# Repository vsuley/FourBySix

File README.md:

# The Ganesha Keyboard

The Ganesha is a keyboard inspired by and forked from the amazing Corne keyboard. After having built a number
of Corne KBs, I need something that has the number row. There are other forks like Lily58 (and further still, like
Sofle, Orbit etc) but they have certain features that I have a strong preference to remove (mirrored PCB, unutilized
component designations, dependence on Pro Micro etc).

## Major Design Goals
### User's POV
1. Split ortho-linear layout.
2. Have a dedicated numbers row.
3. No bigger than a standard print of Moby Dick when packed.
4. Enable USB-C without the added cost of an Elite-C board.
5. Per Key and ambient LEDs.

### Builder's POV
1. Enable factory assembly as much as possible (jlcpcb.com in my case)
2. Clean, self documenting PCB layout.
3. Compatible with low-profile switches and keycaps
4. Directly embedded atmega32u4
5. 4 layer PCB

## Dependencies
### KiCad libraries
You should clone https://github.com/foostan/kbd to get the symbol and footprint libraries used in these kicad projects.
1. Clone this repo and foostan/kbd
1. Install kicad.
1. Open ganesha.pro in Kicad.
1. Preferences > Manage Symbol Libraries
    1.  Hover over the folder looking icon below the table, it should say "Add existing table to library". 
    2.  Click that button.
    3.  Navigate to the symbol library located under kbd/kicad-symbols/
    4.  Add. 
1. Repeat the same process for footprint libraries.

## Starting Priorities
Calling out a few assumptions I will be starting with, but would like to expand when time permits.
1. Kailh Cherry MX hot swap sockets as switch anchors

## Why "Ganesha"?
Ganesha, in Hindu mythology, is the popular elephant headed deity whose images you may have seen. Aside from being the son 
of Lord Shiva, he is also the God of Wisdom and more pertinently, he is the scribe who penned down the great epic 
'Mahabharata' as sage Vyasa composed it.

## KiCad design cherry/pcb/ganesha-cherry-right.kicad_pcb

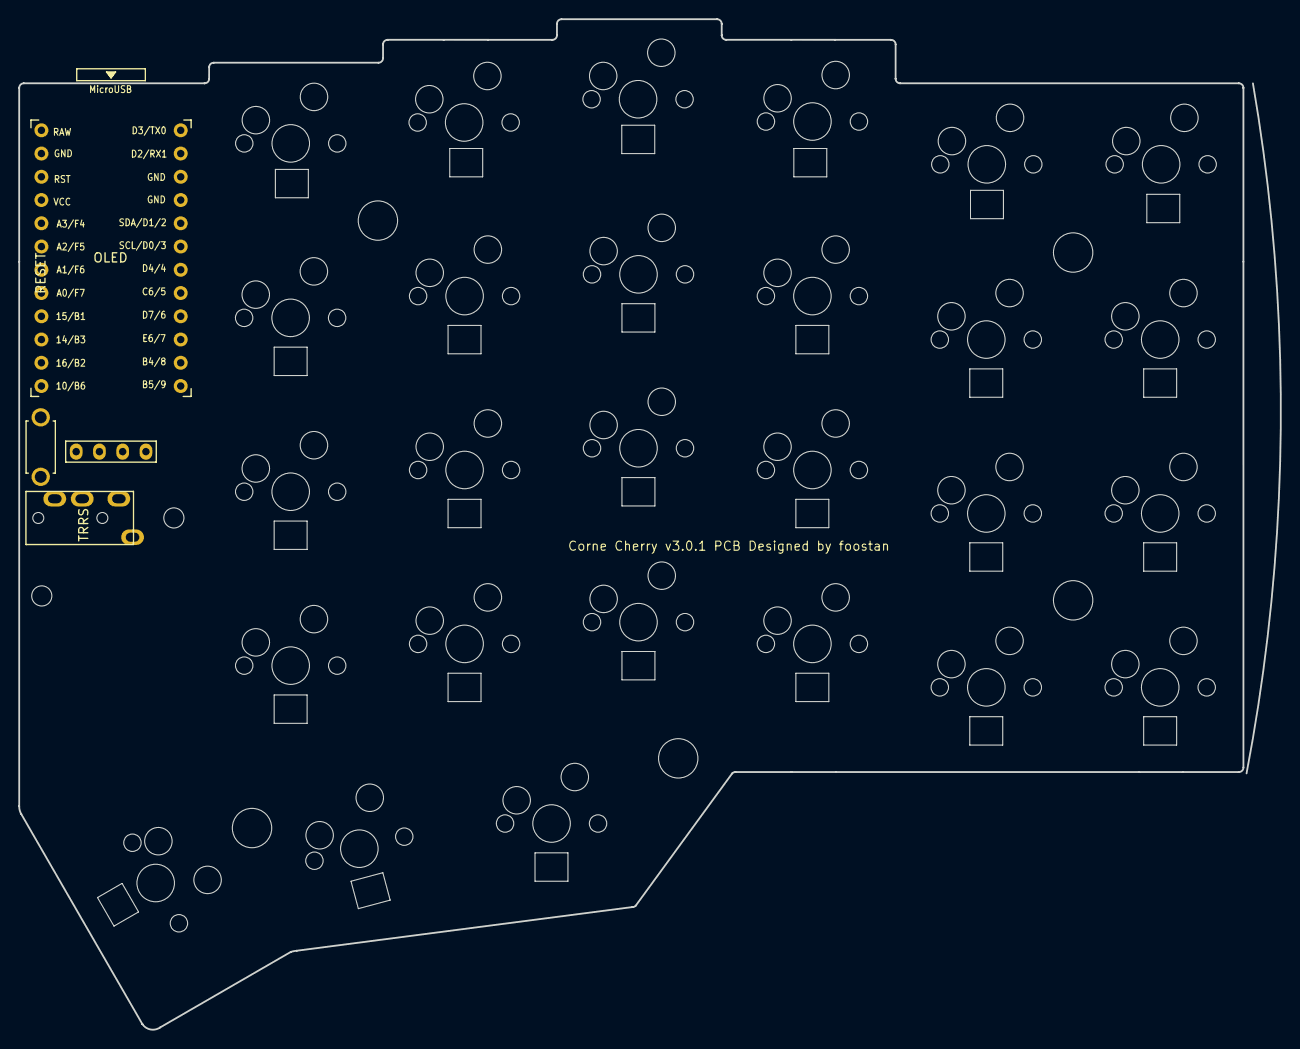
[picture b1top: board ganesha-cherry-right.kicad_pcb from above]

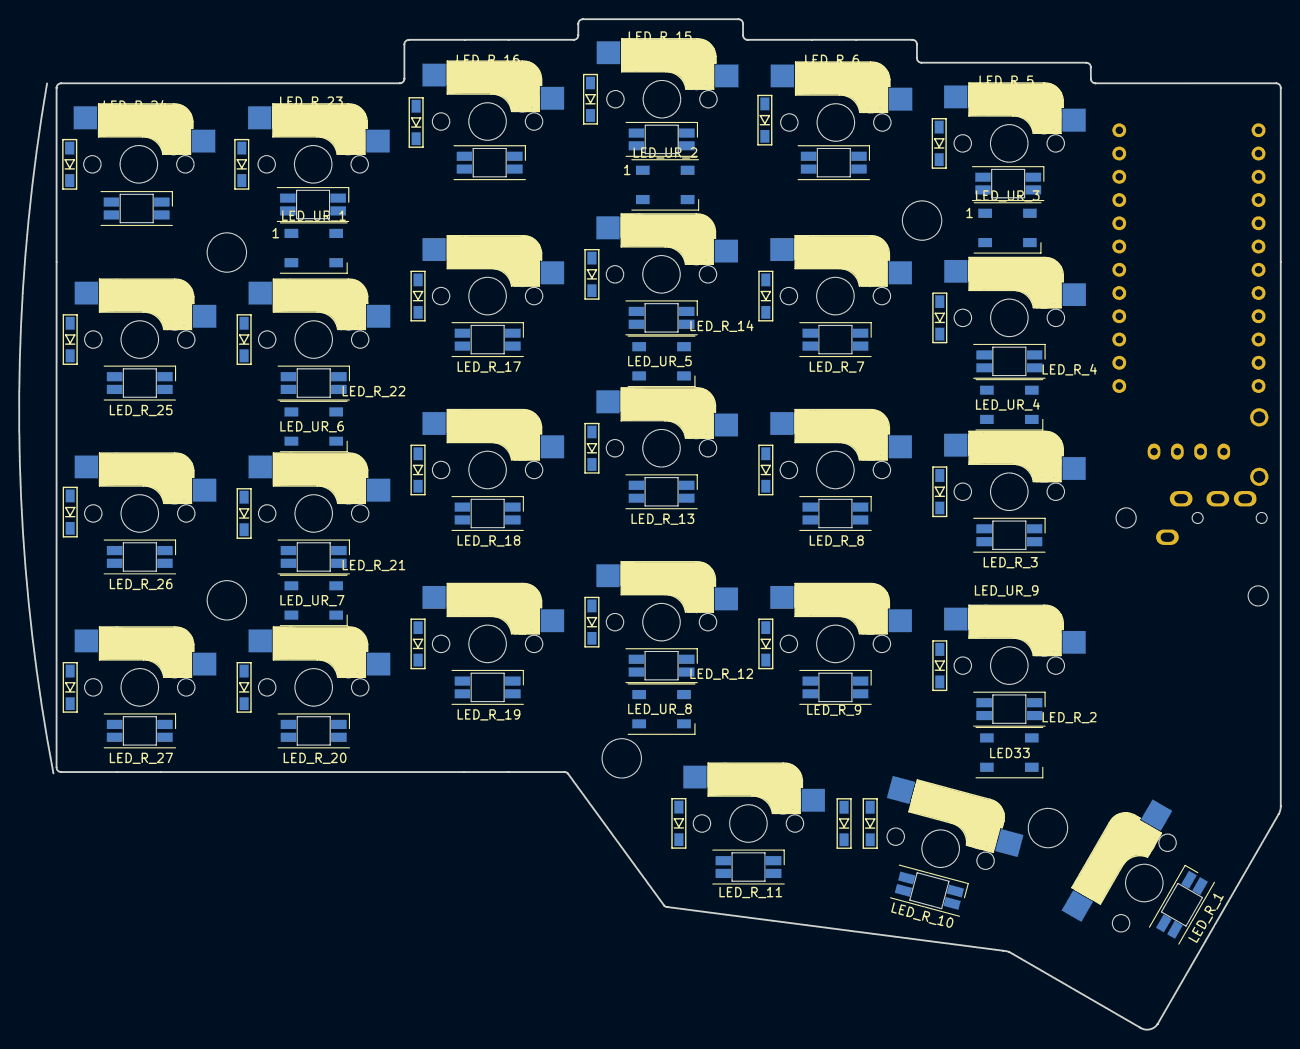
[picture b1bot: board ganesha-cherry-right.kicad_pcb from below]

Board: 2 copper layers, 137.8 x 110.4 mm, 101 parts (66 on the bottom side), 82 nets, no tracks yet.

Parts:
D_R1, D_R2, D_R3, D_R4, D_R5, D_R6, D_R7, D_R8, D_R9, D_R10, D_R11, D_R12, D_R13, D_R14, D_R15, D_R16, D_R17, D_R18, D_R19, D_R20, D_R21, D_R22, D_R23, D_R24, D_R25, D_R26, D_R27: D; D3_SMD_v2
J3: MJ-4PP-9; MJ-4PP-9_1side
J4: OLED; OLED_1side
LED_R_1, LED_R_2, LED_R_3, LED_R_4, LED_R_5, LED_R_6, LED_R_7, LED_R_8, LED_R_9, LED_R_10, LED_R_11, LED_R_12, LED_R_13, LED_R_14, LED_R_15, LED_R_16, LED_R_17, LED_R_18, LED_R_19, LED_R_20, LED_R_21, LED_R_22, LED_R_23, LED_R_24, LED_R_25, LED_R_26, LED_R_27: YS-SK6812MINI-E
LED_UR_1, LED_UR_2, LED_UR_3, LED_UR_4, LED_UR_5, LED_UR_6, LED_UR_7, LED_UR_8, LED_UR_9: WS2812B; LED_WS2812B_PLCC4_5.0x5.0mm_P3.2mm
RSW2: SW_PUSH; ResetSW_1side
Ref**: Val**; M2_HOLE_v2
Ref**#2, Ref**#3, Ref**#4, Ref**#5, Ref**#6, Ref**#7: Val**; M2_HOLE_v2
SW_R1, SW_R2, SW_R3, SW_R4, SW_R5, SW_R6, SW_R7, SW_R8, SW_R9, SW_R10, SW_R11, SW_R12, SW_R13, SW_R14, SW_R15, SW_R16, SW_R17, SW_R18, SW_R19, SW_R20, SW_R21, SW_R22, SW_R23, SW_R24, SW_R25, SW_R26: SW_PUSH; CherryMX_Hotswap
SW_R27: SW_PUSH; CherryMX_Hotswap_1.5u
U2: ProMicro; ProMicro_v3

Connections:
GND: LED_R_1.3, LED_R_2.3, LED_R_3.3, LED_R_4.3, LED_R_5.3, LED_R_6.3, LED_R_7.3, LED_R_8.3, LED_R_9.3, LED_R_10.3, LED_R_11.3, LED_R_12.3, LED_R_13.3, LED_R_14.3, LED_R_15.3, LED_R_16.3, LED_R_17.3, LED_R_18.3, LED_R_19.3, LED_R_20.3, LED_R_21.3, LED_R_22.3, LED_R_23.3, LED_R_24.3, LED_R_25.3, LED_R_26.3, LED_R_27.3, LED_UR_1.3, LED_UR_2.3, LED_UR_3.3, LED_UR_4.3, LED_UR_5.3, LED_UR_6.3, LED_UR_7.3, LED_UR_8.3, LED_UR_9.3
GNDA: J3.C, J4.4, RSW2.2, U2.3, U2.4, U2.23
LED_r: LED_UR_1.4, U2.1
unnamed: D_R1.2, SW_R1.2
unnamed: D_R2.2, SW_R2.2
unnamed: D_R3.2, SW_R3.2
unnamed: D_R4.2, SW_R4.2
unnamed: D_R5.2, SW_R5.2
unnamed: D_R6.2, SW_R6.2
unnamed: D_R7.2, SW_R7.2
unnamed: D_R8.2, SW_R8.2
unnamed: D_R9.2, SW_R9.2
unnamed: D_R10.2, SW_R10.2
unnamed: D_R11.2, SW_R11.2
unnamed: D_R12.2, SW_R12.2
unnamed: D_R13.2, SW_R13.2
unnamed: D_R14.2, SW_R14.2
unnamed: D_R15.2, SW_R15.2
unnamed: D_R16.2, SW_R16.2
unnamed: D_R17.2, SW_R17.2
unnamed: D_R18.2, SW_R18.2
unnamed: D_R19.2, SW_R19.2
unnamed: D_R20.2, SW_R20.2
unnamed: D_R21.2, SW_R21.2
unnamed: D_R22.2, SW_R22.2
unnamed: D_R23.2, SW_R23.2
unnamed: D_R24.2, SW_R24.2
unnamed: D_R25.2, SW_R25.2
unnamed: D_R26.2, SW_R26.2
unnamed: D_R27.2, SW_R27.2
unnamed: LED_R_1.2, LED_R_2.4
unnamed: LED_R_1.4, LED_UR_9.2
unnamed: LED_R_2.2, LED_R_3.4
unnamed: LED_R_3.2, LED_R_4.4
unnamed: LED_R_4.2, LED_R_5.4
unnamed: LED_R_5.2, LED_R_6.4
unnamed: LED_R_6.2, LED_R_7.4
unnamed: LED_R_7.2, LED_R_8.4
unnamed: LED_R_8.2, LED_R_9.4
unnamed: LED_R_10.2, LED_R_11.4
unnamed: LED_R_9.2, LED_R_10.4
unnamed: LED_R_11.2, LED_R_12.4
unnamed: LED_R_12.2, LED_R_13.4
unnamed: LED_R_13.2, LED_R_14.4
unnamed: LED_R_14.2, LED_R_15.4
unnamed: LED_R_15.2, LED_R_16.4
unnamed: LED_R_16.2, LED_R_17.4
unnamed: LED_R_17.2, LED_R_18.4
unnamed: LED_R_18.2, LED_R_19.4
unnamed: LED_R_19.2, LED_R_20.4
unnamed: LED_R_20.2, LED_R_21.4
unnamed: LED_R_21.2, LED_R_22.4
unnamed: LED_R_22.2, LED_R_23.4
unnamed: LED_R_23.2, LED_R_24.4
unnamed: LED_R_24.2, LED_R_25.4
unnamed: LED_R_25.2, LED_R_26.4
unnamed: LED_R_26.2, LED_R_27.4
unnamed: LED_UR_1.2, LED_UR_2.4
unnamed: LED_UR_2.2, LED_UR_3.4
unnamed: LED_UR_3.2, LED_UR_4.4
unnamed: LED_UR_4.2, LED_UR_5.4
unnamed: LED_UR_5.2, LED_UR_6.4
unnamed: LED_UR_6.2, LED_UR_7.4
unnamed: LED_UR_7.2, LED_UR_8.4
unnamed: LED_UR_8.2, LED_UR_9.4
SCL_r: J4.2, U2.6
SDA_r: J4.1, U2.5
VCC: LED_R_1.1, LED_R_2.1, LED_R_3.1, LED_R_4.1, LED_R_5.1, LED_R_6.1, LED_R_7.1, LED_R_8.1, LED_R_9.1, LED_R_10.1, LED_R_11.1, LED_R_12.1, LED_R_13.1, LED_R_14.1, LED_R_15.1, LED_R_16.1, LED_R_17.1, LED_R_18.1, LED_R_19.1, LED_R_20.1, LED_R_21.1, LED_R_22.1, LED_R_23.1, LED_R_24.1, LED_R_25.1, LED_R_26.1, LED_R_27.1, LED_UR_1.1, LED_UR_2.1, LED_UR_3.1, LED_UR_4.1, LED_UR_5.1, LED_UR_6.1, LED_UR_7.1, LED_UR_8.1, LED_UR_9.1
VDD: J3.D, J4.3, U2.21
col0_r: SW_R1.1, SW_R7.1, SW_R13.1, SW_R19.1, U2.20
col1_r: SW_R2.1, SW_R8.1, SW_R14.1, SW_R20.1, U2.19
col2_r: SW_R3.1, SW_R9.1, SW_R15.1, SW_R21.1, SW_R25.1, U2.18
col3_r: SW_R4.1, SW_R10.1, SW_R16.1, SW_R22.1, SW_R26.1, U2.17
col4_r: SW_R5.1, SW_R11.1, SW_R17.1, SW_R23.1, SW_R27.1, U2.16
col5_r: SW_R6.1, SW_R12.1, SW_R18.1, SW_R24.1, U2.15
data_r: J3.B, U2.2
reset_r: RSW2.1, U2.22
row0_r: D_R1.1, D_R2.1, D_R3.1, D_R4.1, D_R5.1, D_R6.1, U2.7
row1_r: D_R7.1, D_R8.1, D_R9.1, D_R10.1, D_R11.1, D_R12.1, U2.8
row2_r: D_R13.1, D_R14.1, D_R15.1, D_R16.1, D_R17.1, D_R18.1, U2.9
row3_r: D_R19.1, D_R20.1, D_R21.1, D_R22.1, D_R23.1, D_R24.1, U2.10
row4_r: D_R25.1, D_R26.1, D_R27.1, U2.11

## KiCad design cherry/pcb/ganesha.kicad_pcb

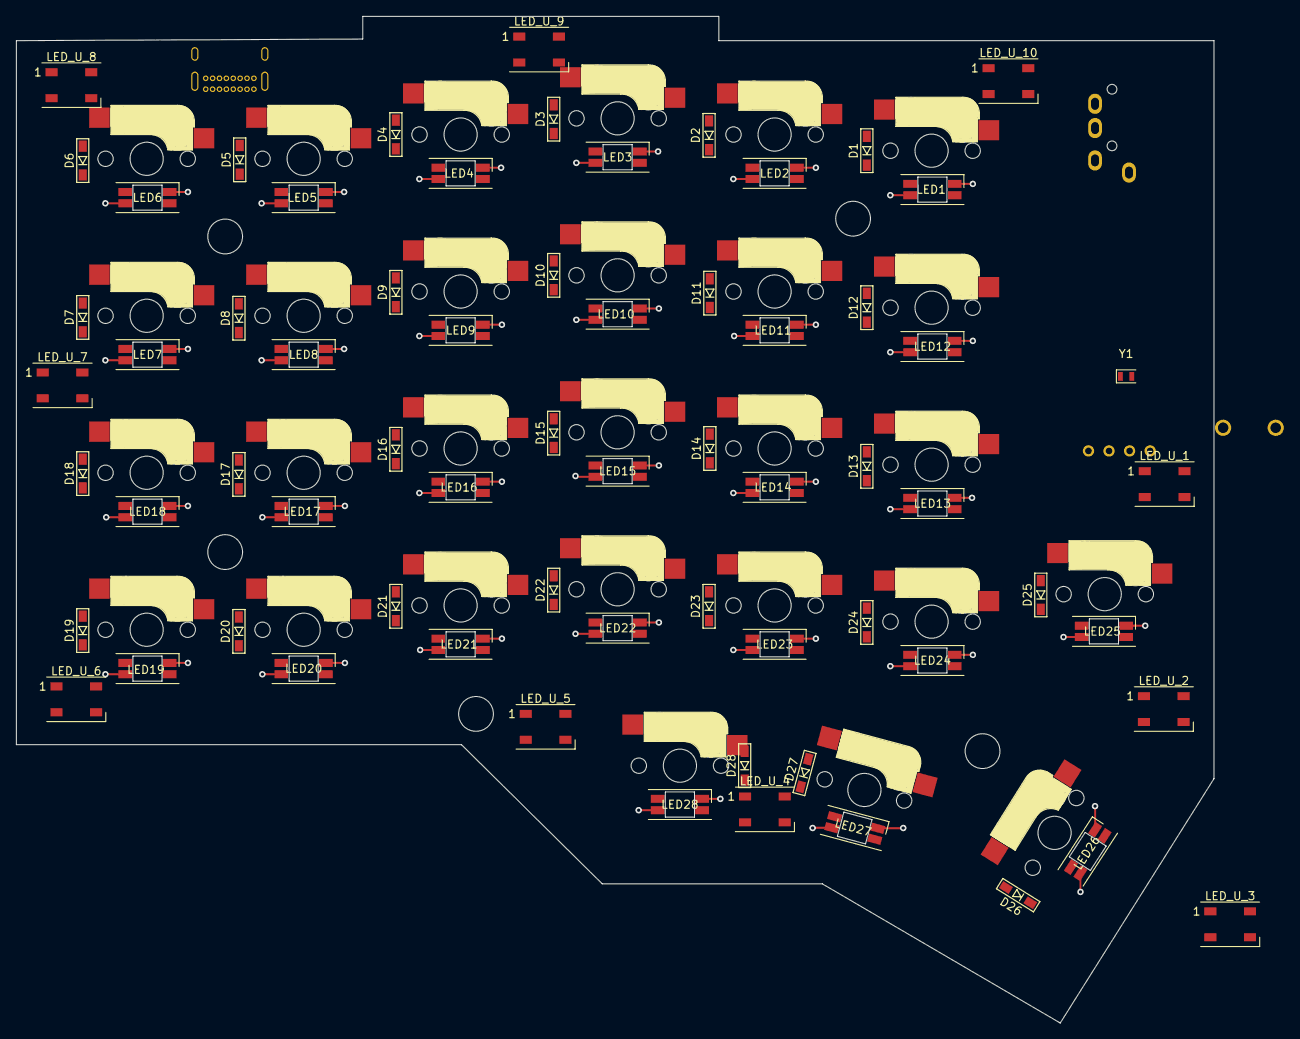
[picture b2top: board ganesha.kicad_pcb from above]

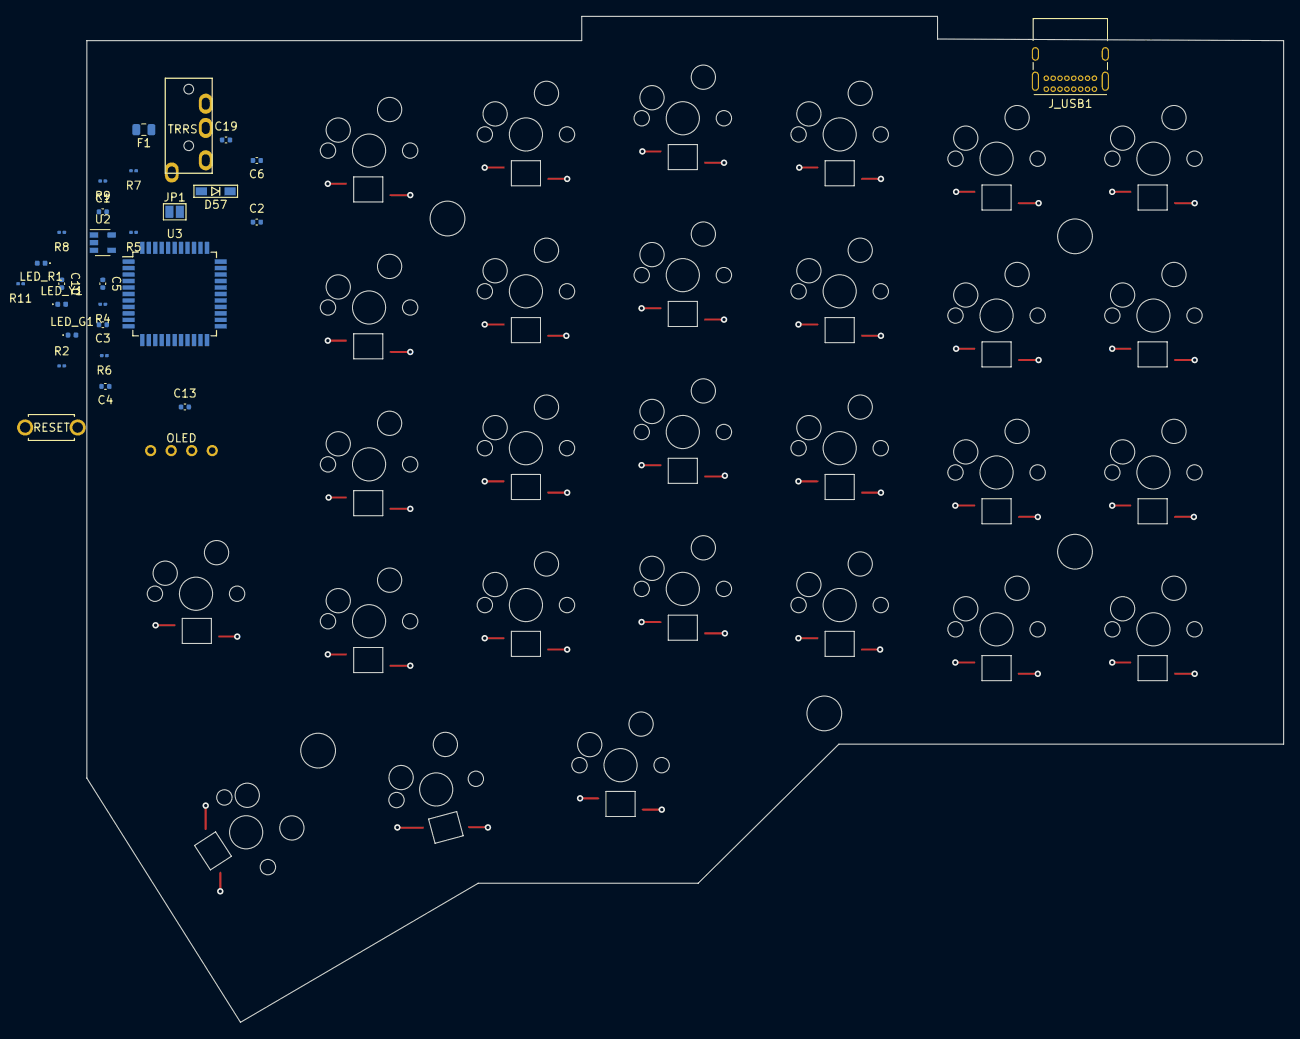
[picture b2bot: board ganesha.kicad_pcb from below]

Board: 4 copper layers, 148.0 x 124.4 mm, 129 parts (57 on the bottom side), 100 nets.

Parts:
C1, C3: 0.1uF; C_0402_1005Metric
C2, C4: 22pF; C_0402_1005Metric
C5, C6, C10: 1uF; C_0402_1005Metric
C13, C19: 10uF; C_0402_1005Metric
D1, D2, D3, D4, D5, D6, D7, D8, D9, D10, D11, D12, D13, D14, D15, D16, D17, D18, D19, D20, D21, D22, D23, D24, D25, D26, D27, D28: D; D3_SMD_v2
D57: Diode; D3_SMD_v2
F1: 500mA; Fuse_0805_2012Metric
J1: MJ-4PP-9; MJ-4PP-9_1side
J2: Conn_01x04; OLED_v2
JP1: Closed for 5V, Open for 3.3V; SolderJumper-2_P1.3mm_Open_Pad1.0x1.5mm
J_USB1: USB_C_Receptacle_USB2.0; USB_C_Receptacle_GCT_USB4085
LED1, LED2, LED3, LED4, LED5, LED6, LED7, LED8, LED9, LED10, LED11, LED12, LED13, LED14, LED15, LED16, LED17, LED18, LED19, LED20, LED21, LED22, LED23, LED24, LED25, LED26, LED27, LED28: YS-SK6812MINI-E
LED_G1: Green; LED_0402_1005Metric
LED_R1: RED; LED_0402_1005Metric
LED_U_1, LED_U_2, LED_U_3, LED_U_4, LED_U_5, LED_U_6, LED_U_7, LED_U_8, LED_U_9, LED_U_10: WS2812B; LED_WS2812B_PLCC4_5.0x5.0mm_P3.2mm
LED_Y1: Yellow; LED_0402_1005Metric
R2: 10K; R_0201_0603Metric
R4, R6: 330; R_0201_0603Metric
R5, R7: 22; R_0201_0603Metric
R8, R9: 5.1K; R_0201_0603Metric
R11: 1K; R_0201_0603Metric
RSW1: SW_Push; ResetSW_1side
Ref**: Val**; M2_HOLE_v2
Ref**#2, Ref**#3, Ref**#4, Ref**#5: Val**; M2_HOLE_v2
SW1, SW2, SW3, SW4, SW5, SW6, SW7, SW8, SW9, SW10, SW11, SW12, SW13, SW14, SW15, SW16, SW17, SW18, SW19, SW20, SW21, SW22, SW23, SW24, SW25, SW27, SW28: SW_PUSH; CherryMX_Hotswap
SW26: SW_PUSH; CherryMX_Hotswap_1.5u
U2: MIC5219-2.5YM5; SOT-23-5
U3: ATmega32U4-AU; TQFP-44_10x10mm_P0.8mm
Y1: 16MHz; Crystal_SMD_2012-2Pin_2.0x1.2mm

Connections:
D+: R5.2, U3.4
D-: R7.2, U3.3
GND: C1.1, C2.1, C3.1, C4.1, C5.1, C6.2, C10.1, C13.2, C19.2, J2.4, J_USB1.A1, J_USB1.A12, J_USB1.B1, J_USB1.B12, J_USB1.S1, LED1.3, LED2.3, LED3.3, LED4.3, LED5.3, LED6.3, LED7.3, LED8.3, LED9.3, LED10.3, LED11.3, LED12.3, LED13.3, LED14.3, LED15.3, LED16.3, LED17.3, LED18.3, LED19.3, LED20.3, LED21.3, LED22.3, LED23.3, LED24.3, LED25.3, LED26.3, LED27.3, LED28.3, LED_R1.1, LED_U_1.3, LED_U_2.3, LED_U_3.3, LED_U_4.3, LED_U_5.3, LED_U_6.3, LED_U_7.3, LED_U_8.3, LED_U_9.3, LED_U_10.3, R8.2, R9.2, RSW1.2, U2.2, U3.5, U3.15, U3.23, U3.33, U3.35, U3.43
unnamed: C1.2, U3.42
unnamed: C2.2, U3.17, Y1.2
unnamed: C4.2, U3.16, Y1.1
unnamed: C5.2, U3.6
unnamed: C19.1, D57.1, U2.1, U2.3
unnamed: D1.2, SW1.2
unnamed: D2.2, SW2.2
unnamed: D3.2, SW3.2
unnamed: D4.2, SW4.2
unnamed: D5.2, SW5.2
unnamed: D6.2, SW6.2
unnamed: D7.2, SW7.2
unnamed: D8.2, SW8.2
unnamed: D9.2, SW9.2
unnamed: D10.2, SW10.2
unnamed: D11.2, SW11.2
unnamed: D12.2, SW12.2
unnamed: D13.2, SW13.2
unnamed: D14.2, SW14.2
unnamed: D15.2, SW15.2
unnamed: D16.2, SW16.2
unnamed: D17.2, SW17.2
unnamed: D18.2, SW18.2
unnamed: D19.2, SW19.2
unnamed: D20.2, SW20.2
unnamed: D21.2, SW21.2
unnamed: D22.2, SW22.2
unnamed: D23.2, SW23.2
unnamed: D24.2, SW24.2
unnamed: D25.2, SW25.2
unnamed: D26.2, SW26.2
unnamed: D27.2, SW27.2
unnamed: D28.2, SW28.2
unnamed: D57.2, F1.2, JP1.1
unnamed: J_USB1.A5, R9.1
unnamed: J_USB1.A6, J_USB1.B6, R5.1
unnamed: J_USB1.A7, J_USB1.B7, R7.1
unnamed: J_USB1.B5, R8.1
unnamed: LED1.2, LED2.4
unnamed: LED1.4, LED_U_10.2
unnamed: LED2.2, LED3.4
unnamed: LED3.2, LED4.4
unnamed: LED4.2, LED5.4
unnamed: LED5.2, LED6.4
unnamed: LED6.2, LED7.4
unnamed: LED7.2, LED8.4
unnamed: LED8.2, LED9.4
unnamed: LED10.2, LED11.4
unnamed: LED9.2, LED10.4
unnamed: LED11.2, LED12.4
unnamed: LED12.2, LED13.4
unnamed: LED13.2, LED14.4
unnamed: LED14.2, LED15.4
unnamed: LED15.2, LED16.4
unnamed: LED16.2, LED17.4
unnamed: LED17.2, LED18.4
unnamed: LED18.2, LED19.4
unnamed: LED19.2, LED20.4
unnamed: LED20.2, LED21.4
unnamed: LED21.2, LED22.4
unnamed: LED22.2, LED23.4
unnamed: LED23.2, LED24.4
unnamed: LED24.2, LED25.4
unnamed: LED25.2, LED26.4
unnamed: LED26.2, LED27.4
unnamed: LED27.2, LED28.4
unnamed: LED_G1.2, R6.2
unnamed: LED_R1.2, R11.2
unnamed: LED_U_1.2, LED_U_2.4
unnamed: LED_U_2.2, LED_U_3.4
unnamed: LED_U_3.2, LED_U_4.4
unnamed: LED_U_4.2, LED_U_5.4
unnamed: LED_U_5.2, LED_U_6.4
unnamed: LED_U_6.2, LED_U_7.4
unnamed: LED_U_7.2, LED_U_8.4
unnamed: LED_U_8.2, LED_U_9.4
unnamed: LED_U_9.2, LED_U_10.4
unnamed: LED_Y1.2, R4.2
unnamed: R4.1, U3.8
unnamed: R6.1, U3.22
RESET: R2.2, RSW1.1, U3.13
SCL: J2.2, U3.18
SDA: J2.1, U3.19
TXO: LED_U_1.4, U3.21
UVCC: C6.1, F1.1, J_USB1.A4, J_USB1.A9, J_USB1.B4, J_USB1.B9
VCC: C3.2, C10.2, C13.1, J2.3, JP1.2, LED1.1, LED2.1, LED3.1, LED4.1, LED5.1, LED6.1, LED7.1, LED8.1, LED9.1, LED10.1, LED11.1, LED12.1, LED13.1, LED14.1, LED15.1, LED16.1, LED17.1, LED18.1, LED19.1, LED20.1, LED21.1, LED22.1, LED23.1, LED24.1, LED25.1, LED26.1, LED27.1, LED28.1, LED_G1.1, LED_U_1.1, LED_U_2.1, LED_U_3.1, LED_U_4.1, LED_U_5.1, LED_U_6.1, LED_U_7.1, LED_U_8.1, LED_U_9.1, LED_U_10.1, LED_Y1.1, R2.1, R11.1, U2.5, U3.2, U3.7, U3.14, U3.24, U3.34, U3.44
col0: SW6.1, SW7.1, SW18.1, SW19.1, U3.39
col1: SW5.1, SW8.1, SW17.1, SW20.1, U3.38
col2: SW4.1, SW9.1, SW16.1, SW21.1, SW28.1, U3.37
col3: SW3.1, SW10.1, SW15.1, SW22.1, SW27.1, U3.36
col4: SW2.1, SW11.1, SW14.1, SW23.1, SW26.1, U3.9
col5: SW1.1, SW12.1, SW13.1, SW24.1, SW25.1, U3.11
row0: D1.1, D2.1, D3.1, D4.1, D5.1, D6.1, U3.25
row1: D7.1, D8.1, D9.1, D10.1, D11.1, D12.1, U3.31
row2: D13.1, D14.1, D15.1, D16.1, D17.1, D18.1, U3.27
row3: D19.1, D20.1, D21.1, D22.1, D23.1, D24.1, U3.1
row4: D25.1, D26.1, D27.1, D28.1, U3.28

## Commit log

2021-03-10 Removed extraneous folders. Initial schematic with embedded ATMega
2021-03-10 Brendan review updates
2021-03-16 Minor updates
2021-03-17 rules inspector mostly satisfied. Ready for PCB design
2021-03-19 Update README.md
    Renaming
2021-03-19 renaming related changes. Also addind gitignore.
2021-03-19 no need to save temp kicad files
2021-03-19 Delete corne-cherry directory
    No longer need the reference. Removing.
2021-03-19 Delete doc directory
    The documentation here no longer applies to this project due to the changes in Ganesha. Removing. Will re-add with correct assets later.
2021-03-19 Delete plates directory
    This content no longer applies. Removing. Will re-add for Ganesha-specific plates later.
2021-03-19 Update README.md
    Adding instructions to add Kicad libraries.
2021-03-24 Started PCB design. Marking territory only so far.
2021-03-25 Tightened up layout. Added rough cut edge.
2021-12-01 Part I of adding row 4
    Moved some files around for better organization.
    Added footprints for row 4. Looking good! Need to figure out the rats nest and connections next. Diodes need to be renamed as well.
2021-12-01 Adding kicadhelper.py
2021-12-02 Layout Done, about to blow away previous tracks
2021-12-02 Left side tracks are routed! Need review.
2021-12-03 Splitting keyboard into two halves at file level.
2021-12-06 minor revs and adding some design goals
